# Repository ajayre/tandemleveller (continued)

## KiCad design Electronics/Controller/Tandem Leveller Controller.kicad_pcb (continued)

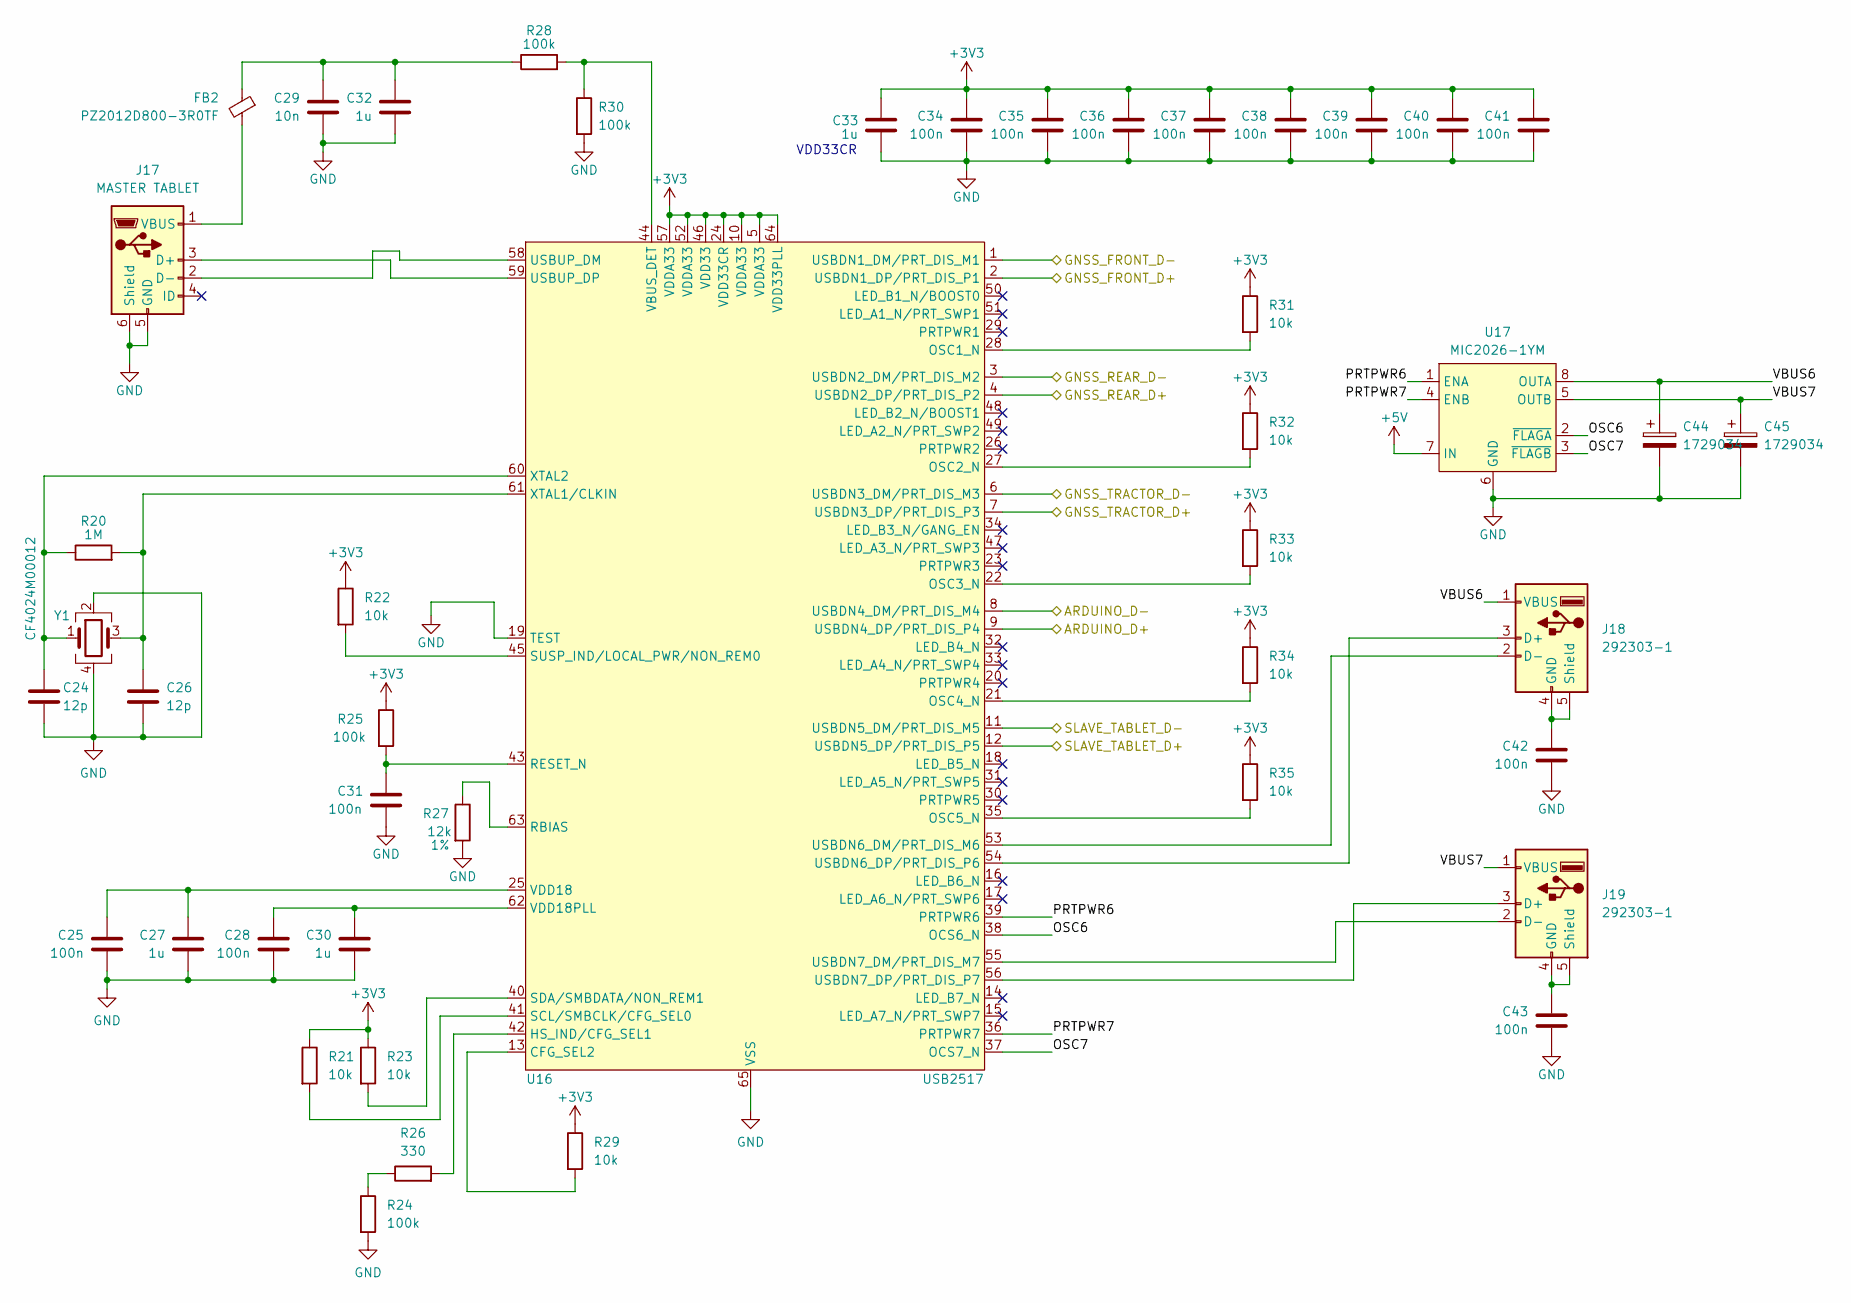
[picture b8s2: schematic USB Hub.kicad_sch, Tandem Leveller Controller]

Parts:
C24, C26: 12p; C_0805_2012Metric; LCSC C1792
C25, C28, C31, C34, C35, C36, C37, C38, C39, C40, C41, C42, C43: 100n; C_0805_2012Metric; LCSC C1711
C27, C30, C32, C33: 1u; C_0805_2012Metric; LCSC C24123
C29: 10n; C_0805_2012Metric; LCSC C1710
C44, C45: 1729034; CP_Elec_6.3x5.9; LCSC C340733
FB2: PZ2012D800-3R0TF; R_0805_2012Metric; LCSC C12389
J17: MASTER TABLET; USB_Micro-B_Amphenol_10103594-0001LF_Horizontal; LCSC C428495
J18, J19: 292303-1; LCSC C86461
R20: 1M; R_0805_2012Metric; LCSC C17514
R21, R22, R23, R29, R31, R32, R33, R34, R35: 10k; R_0805_2012Metric; LCSC C17414
R24, R25, R28, R30: 100k; R_0805_2012Metric; LCSC C17407
R26: 330; R_0805_2012Metric; LCSC C17630
R27: 12k; R_0805_2012Metric; Tolerance 1%; LCSC C17444
U16: USB2517; QFN-64-1EP_9x9mm_P0.5mm_EP4.7x4.7mm_ThermalVias; LCSC C1521556
U17: MIC2026-1YM; SOIC-8_3.9x4.9mm_P1.27mm; LCSC C144190
Y1: CF4024M00012; FA-238; LCSC C5765976

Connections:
+3V3: C33.1, C34.1, C35.1, C36.1, C37.1, C38.1, C39.1, C40.1, C41.1, R21.1, R22.1, R23.1, R25.1, R29.1, R31.1, R32.1, R33.1, R34.1, R35.1, U16.5 (VDDA33), U16.10 (VDDA33), U16.24 (VDD33CR), U16.46 (VDD33), U16.52 (VDDA33), U16.57 (VDDA33), U16.64 (VDD33PLL); also elsewhere on the board
+5V: U17.7 (IN); also elsewhere on the board
/Slave Tablet/SLAVE_TABLET_D+: U16.12 (USBDN5_DP/PRT_DIS_P5); also elsewhere on the board
/Slave Tablet/SLAVE_TABLET_D-: U16.11 (USBDN5_DM/PRT_DIS_M5); also elsewhere on the board
/USB Devices/ARDUINO_D+: U16.9 (USBDN4_DP/PRT_DIS_P4); also elsewhere on the board
/USB Devices/ARDUINO_D-: U16.8 (USBDN4_DM/PRT_DIS_M4); also elsewhere on the board
/USB Devices/GNSS_FRONT_D+: U16.2 (USBDN1_DP/PRT_DIS_P1); also elsewhere on the board
/USB Devices/GNSS_FRONT_D-: U16.1 (USBDN1_DM/PRT_DIS_M1); also elsewhere on the board
/USB Devices/GNSS_REAR_D+: U16.4 (USBDN2_DP/PRT_DIS_P2); also elsewhere on the board
/USB Devices/GNSS_REAR_D-: U16.3 (USBDN2_DM/PRT_DIS_M2); also elsewhere on the board
/USB Devices/GNSS_TRACTOR_D+: U16.7 (USBDN3_DP/PRT_DIS_P3); also elsewhere on the board
/USB Devices/GNSS_TRACTOR_D-: U16.6 (USBDN3_DM/PRT_DIS_M3); also elsewhere on the board
/USB Hub/OSC6: U16.38 (OCS6_N), U17.2 (~FLAGA)
/USB Hub/OSC7: U16.37 (OCS7_N), U17.3 (~FLAGB)
/USB Hub/PRTPWR6: U16.39 (PRTPWR6), U17.1 (ENA)
/USB Hub/PRTPWR7: U16.36 (PRTPWR7), U17.4 (ENB)
/USB Hub/VBUS6: C44.1, J18.1 (VBUS), U17.8 (OUTA)
/USB Hub/VBUS7: C45.1, J19.1 (VBUS), U17.5 (OUTB)
GND: C24.2, C25.2, C26.2, C27.2, C28.2, C29.2, C30.2, C31.2, C32.2, C33.2, C34.2, C35.2, C36.2, C37.2, C38.2, C39.2, C40.2, C41.2, C42.2, C43.2, C44.2, C45.2, J17.5 (GND), J17.6 (Shield), R24.2, R27.2, R30.2, U16.19 (TEST), U16.65 (VSS), U17.6 (GND), Y1.2, Y1.4; also elsewhere on the board
unnamed: C29.1, C32.1, FB2.1, R28.1
unnamed: J17.3 (D+), U16.59 (USBUP_DP)
unnamed: J17.2 (D-), U16.58 (USBUP_DM)
unnamed: FB2.2, J17.1 (VBUS)
unnamed: J18.3 (D+), U16.54 (USBDN6_DP/PRT_DIS_P6)
unnamed: J18.2 (D-), U16.53 (USBDN6_DM/PRT_DIS_M6)
unnamed: C42.1, J18.4 (GND), J18.5 (Shield)
unnamed: J19.3 (D+), U16.56 (USBDN7_DP/PRT_DIS_P7)
unnamed: J19.2 (D-), U16.55 (USBDN7_DM/PRT_DIS_M7)
unnamed: C43.1, J19.4 (GND), J19.5 (Shield)
unnamed: R24.1, R26.1
unnamed: R29.2, U16.13 (CFG_SEL2)
unnamed: R26.2, U16.42 (HS_IND/CFG_SEL1)
unnamed: R31.2, U16.28 (OSC1_N)
unnamed: R32.2, U16.27 (OSC2_N)
unnamed: R33.2, U16.22 (OSC3_N)
unnamed: R34.2, U16.21 (OSC4_N)
unnamed: R35.2, U16.35 (OSC5_N)
unnamed: R27.1, U16.63 (RBIAS)
unnamed: C31.1, R25.2, U16.43 (RESET_N)
unnamed: R21.2, U16.41 (SCL/SMBCLK/CFG_SEL0)
unnamed: R23.2, U16.40 (SDA/SMBDATA/NON_REM1)
unnamed: R22.2, U16.45 (SUSP_IND/LOCAL_PWR/NON_REM0)
unnamed: R28.2, R30.1, U16.44 (VBUS_DET)
unnamed: C25.1, C27.1, U16.25 (VDD18)
unnamed: C28.1, C30.1, U16.62 (VDD18PLL)
unnamed: C26.1, R20.2, U16.61 (XTAL1/CLKIN), Y1.3
unnamed: C24.1, R20.1, U16.60 (XTAL2), Y1.1

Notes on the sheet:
VDD33CR

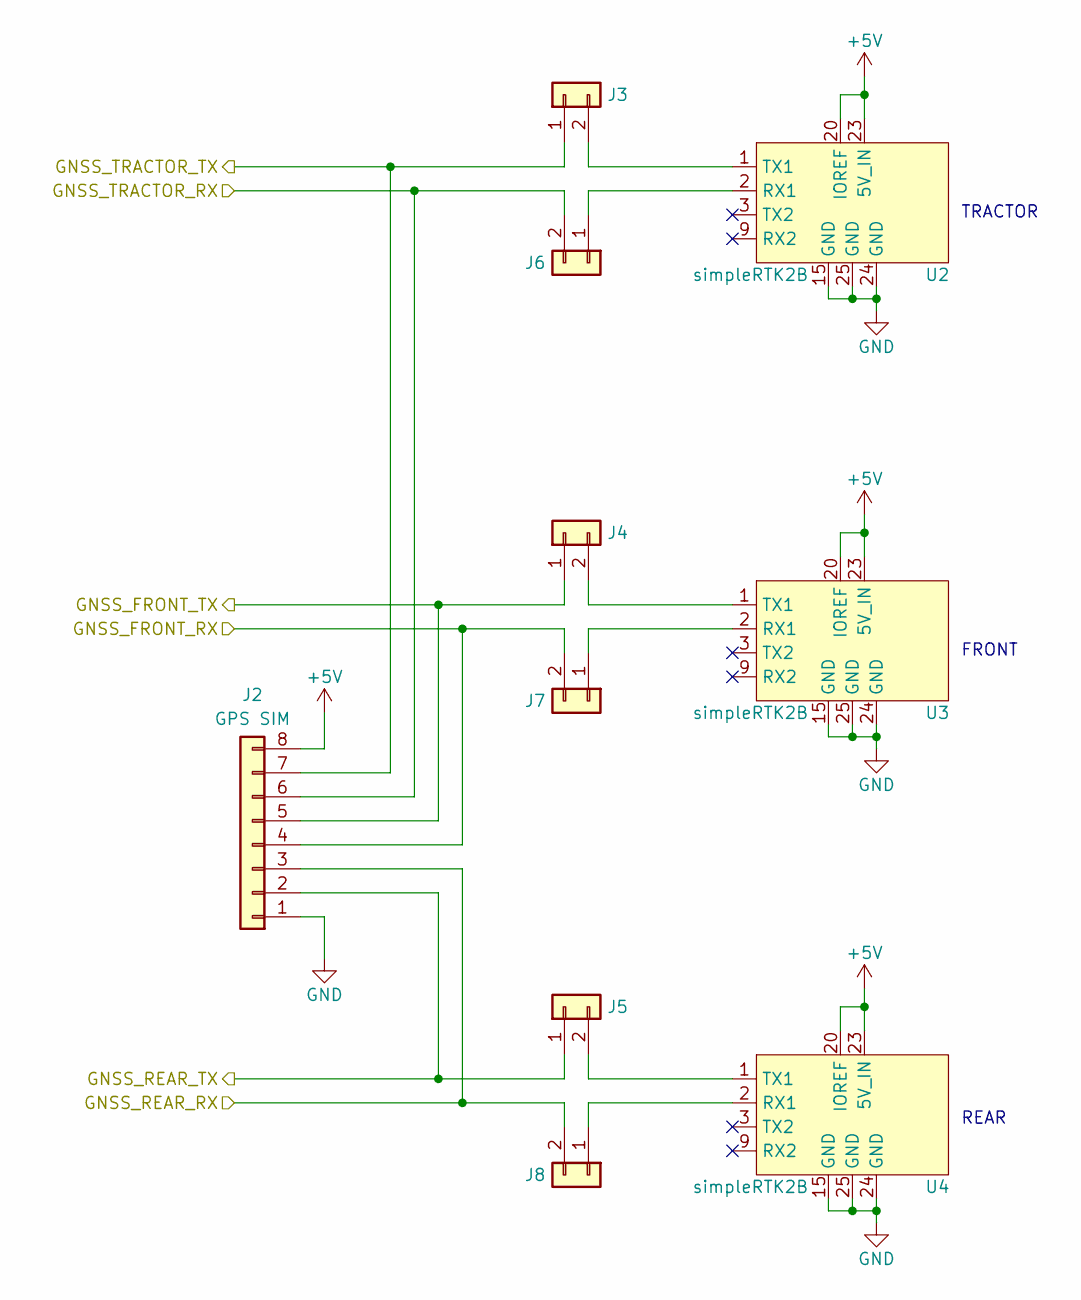
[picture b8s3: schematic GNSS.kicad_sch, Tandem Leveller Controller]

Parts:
J2: GPS SIM; JST_PH_B8B-PH-K_1x08_P2.00mm_Vertical; LCSC C157974
J3, J4, J5, J6, J7, J8: Conn_01x02; PinHeader_1x02_P2.54mm_Vertical; LCSC C7494857
U2, U3, U4: simpleRTK2B

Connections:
+5V: J2.8, U2.20 (IOREF), U2.23 (5V_IN), U3.20 (IOREF), U3.23 (5V_IN), U4.20 (IOREF), U4.23 (5V_IN); also elsewhere on the board
/GNSS/GNSS_FRONT_RX: J2.4, J7.2; also elsewhere on the board
/GNSS/GNSS_FRONT_TX: J2.5, J4.1; also elsewhere on the board
/GNSS/GNSS_REAR_RX: J2.3, J8.2; also elsewhere on the board
/GNSS/GNSS_REAR_TX: J2.2, J5.1; also elsewhere on the board
/GNSS/GNSS_TRACTOR_RX: J2.6, J6.2; also elsewhere on the board
/GNSS/GNSS_TRACTOR_TX: J2.7, J3.1; also elsewhere on the board
GND: J2.1, U2.15 (GND), U2.24 (GND), U2.25 (GND), U3.15 (GND), U3.24 (GND), U3.25 (GND), U4.15 (GND), U4.24 (GND), U4.25 (GND); also elsewhere on the board
unnamed: J3.2, U2.1 (TX1)
unnamed: J4.2, U3.1 (TX1)
unnamed: J5.2, U4.1 (TX1)
unnamed: J6.1, U2.2 (RX1)
unnamed: J7.1, U3.2 (RX1)
unnamed: J8.1, U4.2 (RX1)

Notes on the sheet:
FRONT
REAR
TRACTOR

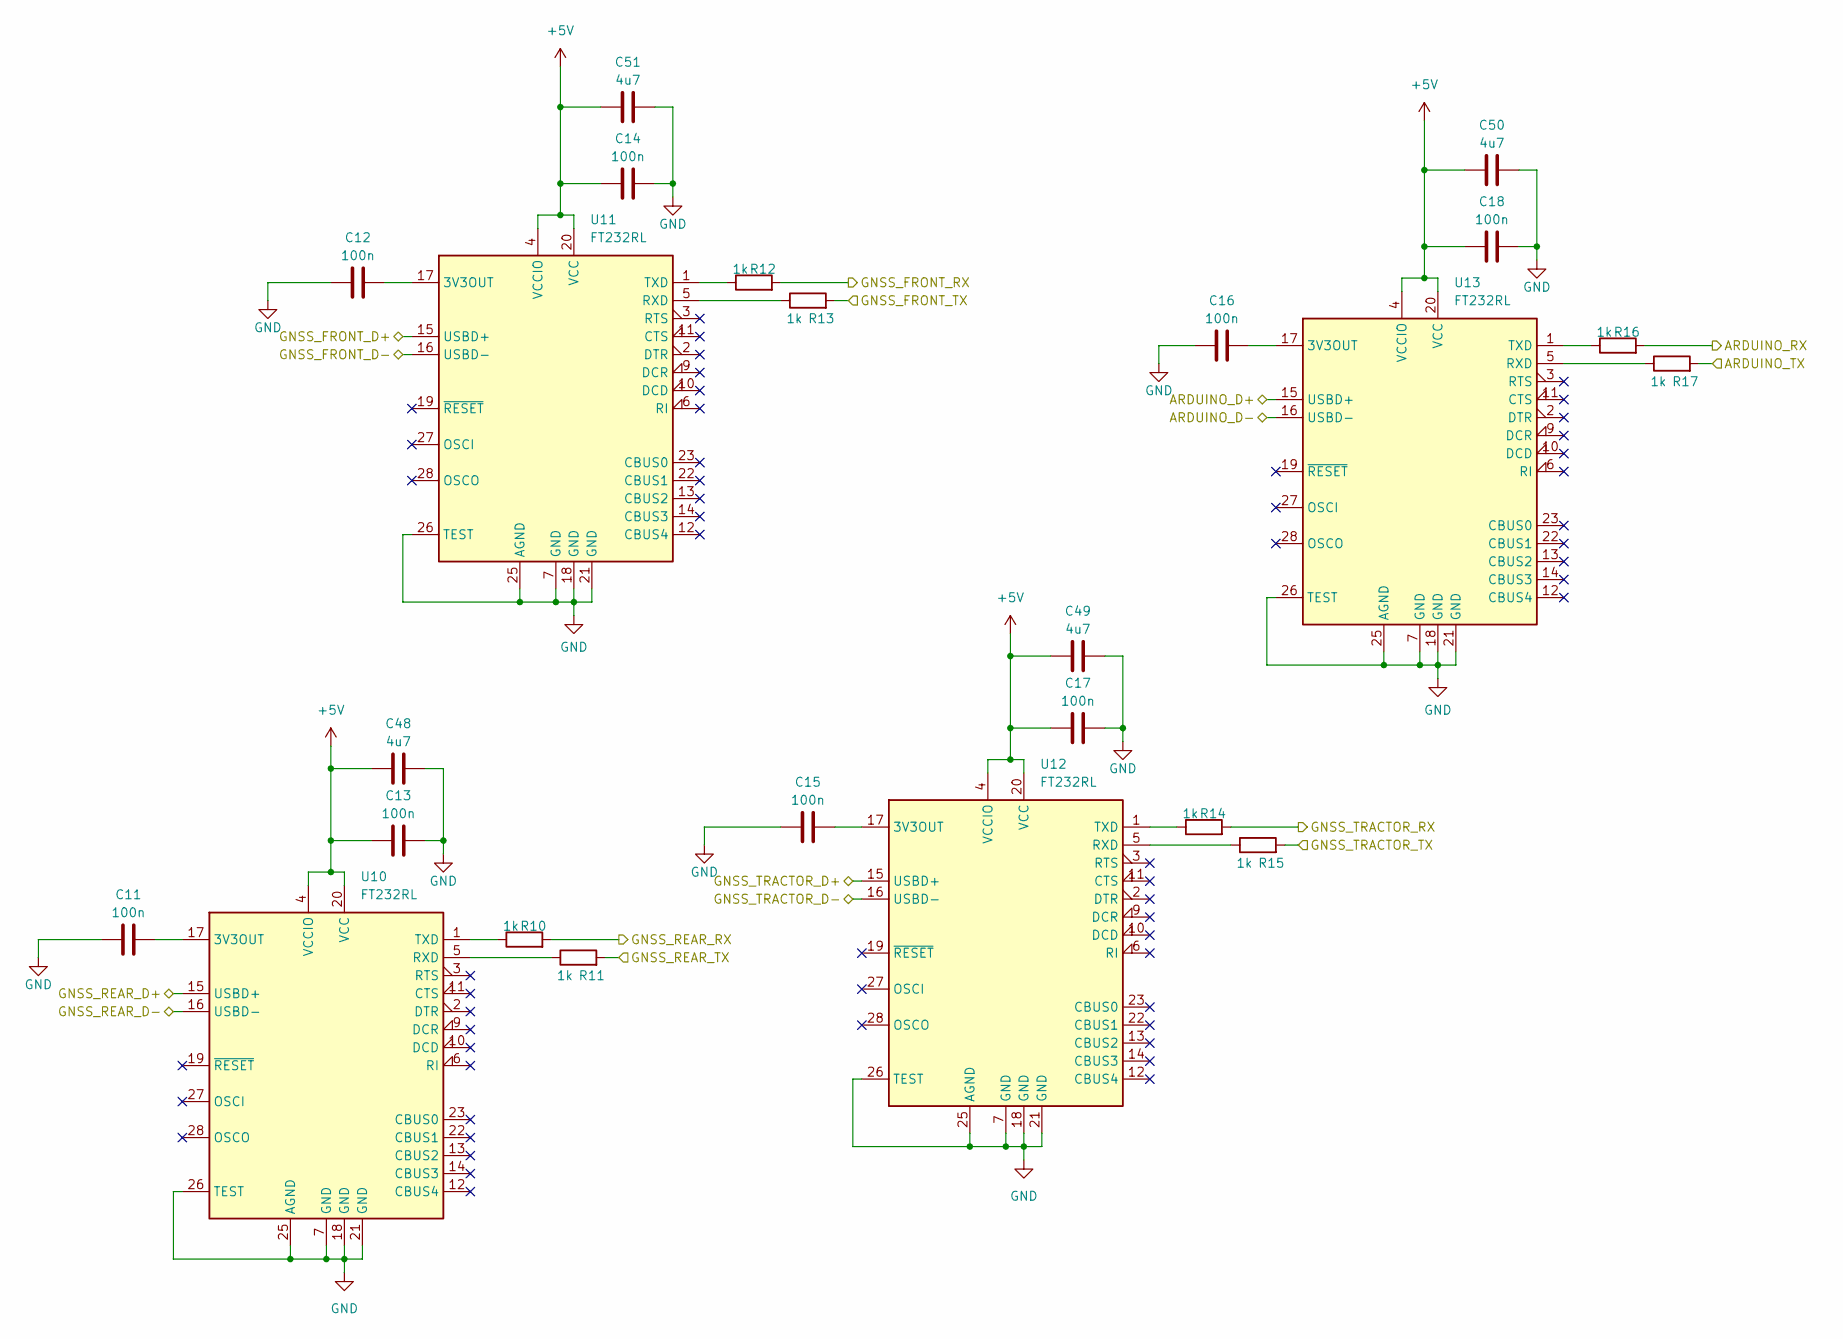
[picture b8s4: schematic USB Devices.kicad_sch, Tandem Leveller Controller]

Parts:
C11, C12, C13, C14, C15, C16, C17, C18: 100n; C_0805_2012Metric; LCSC C1711
C48, C49, C50, C51: 4u7; C_0805_2012Metric; LCSC C1779
R10, R11, R12, R13, R14, R15, R16, R17: 1k; R_0805_2012Metric; LCSC C17513
U10, U11, U12, U13: FT232RL; SSOP-28_5.3x10.2mm_P0.65mm; LCSC C8690

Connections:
+5V: C13.1, C14.1, C17.1, C18.1, C48.1, C49.1, C50.1, C51.1, U10.4 (VCCIO), U10.20 (VCC), U11.4 (VCCIO), U11.20 (VCC), U12.4 (VCCIO), U12.20 (VCC), U13.4 (VCCIO), U13.20 (VCC); also elsewhere on the board
/GNSS/GNSS_FRONT_RX: R12.2; also elsewhere on the board
/GNSS/GNSS_FRONT_TX: R13.2; also elsewhere on the board
/GNSS/GNSS_REAR_RX: R10.2; also elsewhere on the board
/GNSS/GNSS_REAR_TX: R11.2; also elsewhere on the board
/GNSS/GNSS_TRACTOR_RX: R14.2; also elsewhere on the board
/GNSS/GNSS_TRACTOR_TX: R15.2; also elsewhere on the board
/USB Devices/ARDUINO_D+: U13.15 (USBD+); also elsewhere on the board
/USB Devices/ARDUINO_D-: U13.16 (USBD-); also elsewhere on the board
/USB Devices/ARDUINO_RX: R16.2; also elsewhere on the board
/USB Devices/ARDUINO_TX: R17.2; also elsewhere on the board
/USB Devices/GNSS_FRONT_D+: U11.15 (USBD+); also elsewhere on the board
/USB Devices/GNSS_FRONT_D-: U11.16 (USBD-); also elsewhere on the board
/USB Devices/GNSS_REAR_D+: U10.15 (USBD+); also elsewhere on the board
/USB Devices/GNSS_REAR_D-: U10.16 (USBD-); also elsewhere on the board
/USB Devices/GNSS_TRACTOR_D+: U12.15 (USBD+); also elsewhere on the board
/USB Devices/GNSS_TRACTOR_D-: U12.16 (USBD-); also elsewhere on the board
GND: C11.1, C12.1, C13.2, C14.2, C15.1, C16.1, C17.2, C18.2, C48.2, C49.2, C50.2, C51.2, U10.7 (GND), U10.18 (GND), U10.21 (GND), U10.25 (AGND), U10.26 (TEST), U11.7 (GND), U11.18 (GND), U11.21 (GND), U11.25 (AGND), U11.26 (TEST), U12.7 (GND), U12.18 (GND), U12.21 (GND), U12.25 (AGND), U12.26 (TEST), U13.7 (GND), U13.18 (GND), U13.21 (GND), U13.25 (AGND), U13.26 (TEST); also elsewhere on the board
unnamed: C11.2, U10.17 (3V3OUT)
unnamed: R11.1, U10.5 (RXD)
unnamed: R10.1, U10.1 (TXD)
unnamed: C12.2, U11.17 (3V3OUT)
unnamed: R13.1, U11.5 (RXD)
unnamed: R12.1, U11.1 (TXD)
unnamed: C15.2, U12.17 (3V3OUT)
unnamed: R15.1, U12.5 (RXD)
unnamed: R14.1, U12.1 (TXD)
unnamed: C16.2, U13.17 (3V3OUT)
unnamed: R17.1, U13.5 (RXD)
unnamed: R16.1, U13.1 (TXD)

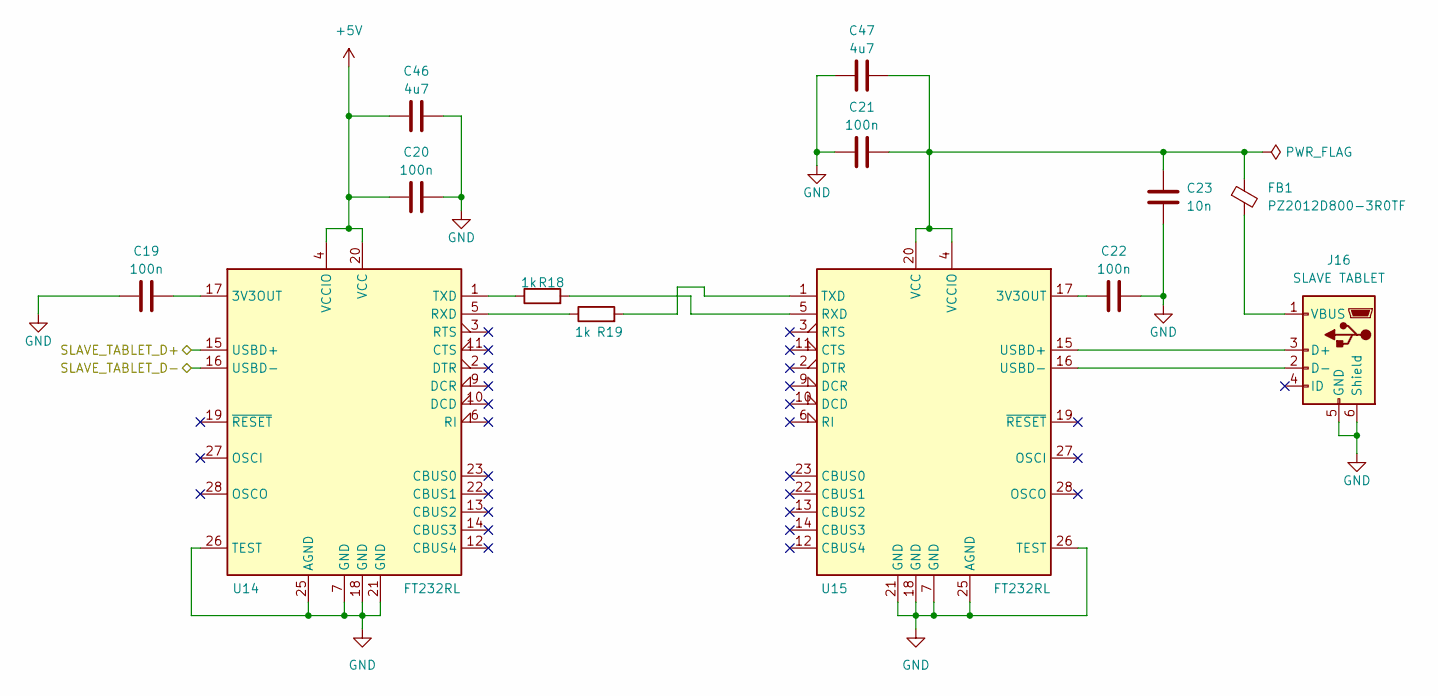
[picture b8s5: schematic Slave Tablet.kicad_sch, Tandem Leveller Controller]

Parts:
C19, C20, C21, C22: 100n; C_0805_2012Metric; LCSC C1711
C23: 10n; C_0805_2012Metric; LCSC C1710
C46, C47: 4u7; C_0805_2012Metric; LCSC C1779
FB1: PZ2012D800-3R0TF; R_0805_2012Metric; LCSC C12389
J16: SLAVE TABLET; USB_Micro-B_Amphenol_10103594-0001LF_Horizontal; LCSC C428495
R18, R19: 1k; R_0805_2012Metric; LCSC C17513
U14, U15: FT232RL; SSOP-28_5.3x10.2mm_P0.65mm; LCSC C8690

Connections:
+5V: C20.1, C46.1, U14.4 (VCCIO), U14.20 (VCC); also elsewhere on the board
/Slave Tablet/SLAVE_TABLET_D+: U14.15 (USBD+); also elsewhere on the board
/Slave Tablet/SLAVE_TABLET_D-: U14.16 (USBD-); also elsewhere on the board
GND: C19.1, C20.2, C21.2, C22.1, C23.2, C46.2, C47.1, J16.5 (GND), J16.6 (Shield), U14.7 (GND), U14.18 (GND), U14.21 (GND), U14.25 (AGND), U14.26 (TEST), U15.7 (GND), U15.18 (GND), U15.21 (GND), U15.25 (AGND), U15.26 (TEST); also elsewhere on the board
unnamed: J16.3 (D+), U15.15 (USBD+)
unnamed: J16.2 (D-), U15.16 (USBD-)
unnamed: FB1.2, J16.1 (VBUS)
unnamed: C19.2, U14.17 (3V3OUT)
unnamed: R19.1, U14.5 (RXD)
unnamed: R18.1, U14.1 (TXD)
unnamed: C22.2, U15.17 (3V3OUT)
unnamed: R18.2, U15.5 (RXD)
unnamed: R19.2, U15.1 (TXD)
unnamed: C21.1, C23.1, C47.2, FB1.1, U15.4 (VCCIO), U15.20 (VCC)

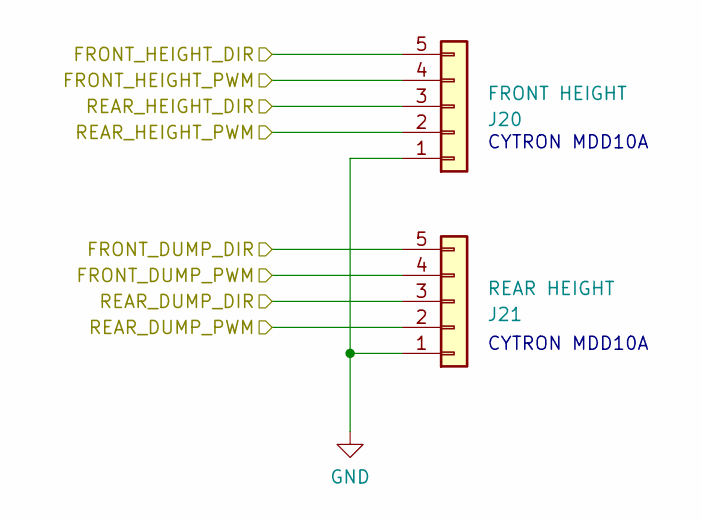
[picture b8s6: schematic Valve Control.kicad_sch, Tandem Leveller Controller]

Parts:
J20: FRONT HEIGHT; JST_PH_B5B-PH-K_1x05_P2.00mm_Vertical; LCSC C157993
J21: REAR HEIGHT; JST_PH_B5B-PH-K_1x05_P2.00mm_Vertical; LCSC C157993

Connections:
/Valve Control/FRONT_DUMP_DIR: J21.5; also elsewhere on the board
/Valve Control/FRONT_DUMP_PWM: J21.4; also elsewhere on the board
/Valve Control/FRONT_HEIGHT_DIR: J20.5; also elsewhere on the board
/Valve Control/FRONT_HEIGHT_PWM: J20.4; also elsewhere on the board
/Valve Control/REAR_DUMP_DIR: J21.3; also elsewhere on the board
/Valve Control/REAR_DUMP_PWM: J21.2; also elsewhere on the board
/Valve Control/REAR_HEIGHT_DIR: J20.3; also elsewhere on the board
/Valve Control/REAR_HEIGHT_PWM: J20.2; also elsewhere on the board
GND: J20.1, J21.1; also elsewhere on the board

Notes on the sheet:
CYTRON MDD10A

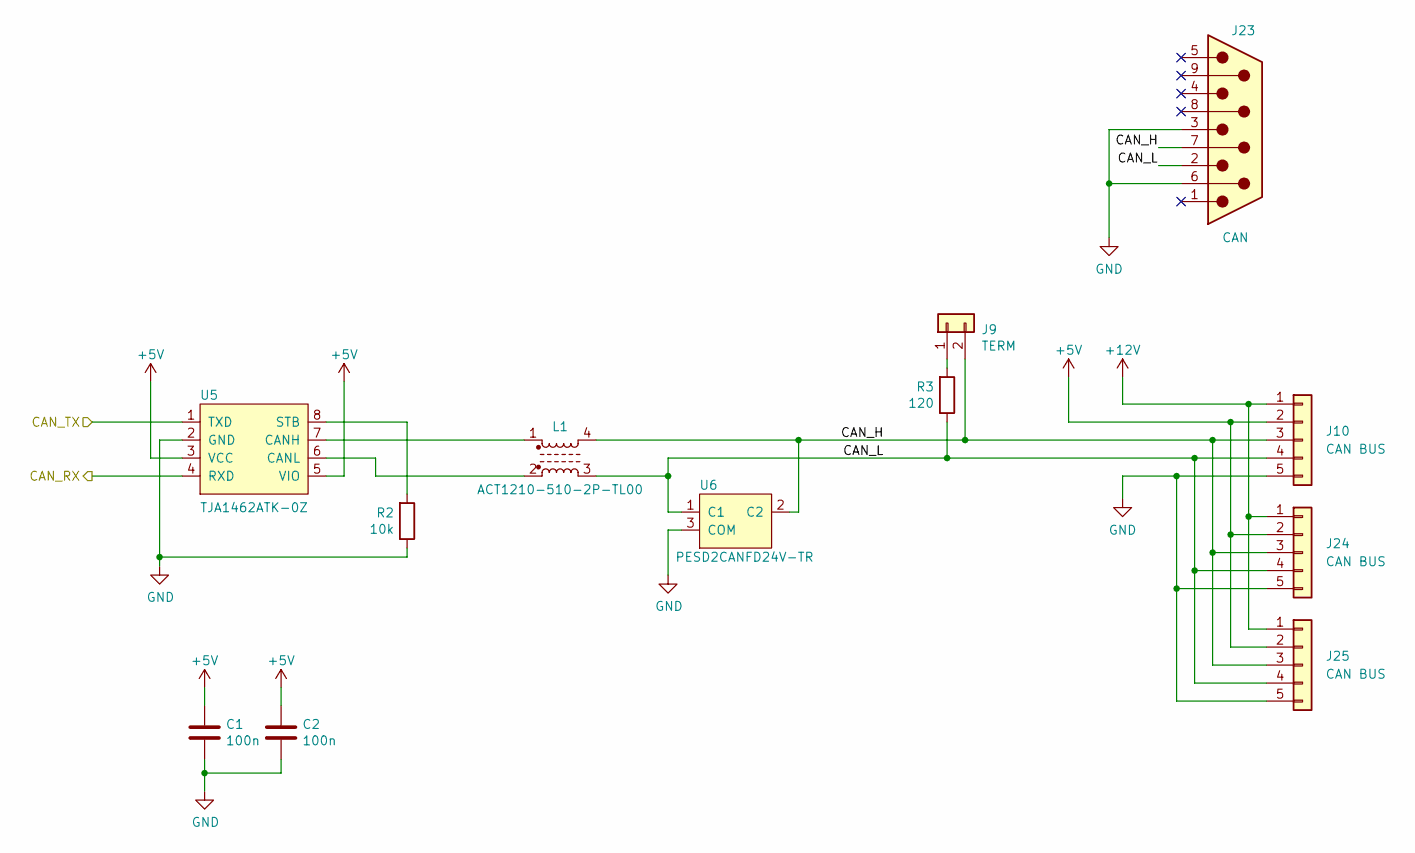
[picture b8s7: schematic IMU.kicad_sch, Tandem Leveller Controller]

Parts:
C1, C2: 100n; C_0805_2012Metric; LCSC C1711
J9: TERM; PinHeader_1x02_P2.54mm_Vertical; LCSC C7494857
J10, J24, J25: CAN BUS; JST_PH_B5B-PH-K_1x05_P2.00mm_Vertical; LCSC C157993
J23: CAN; DB9_RA_MALE_LD09P13A4; LCSC C3103673
L1: ACT1210-510-2P-TL00; LCSC C95572
R2: 10k; R_0805_2012Metric; LCSC C17414
R3: 120; R_0805_2012Metric; LCSC C17437
U5: TJA1462ATK-0Z; HVSON8_0_65mm; LCSC C3229259
U6: PESD2CANFD24V-TR; SOT-23; LCSC C552486

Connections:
+5V: C1.1, C2.1, J10.2, J24.2, J25.2, U5.3 (VCC), U5.5 (VIO); also elsewhere on the board
+12V: J10.1, J24.1, J25.1; also elsewhere on the board
/CAN/CAN_H: J9.2, J10.3, J23.7, J24.3, J25.3, L1.4, U6.2 (C2)
/CAN/CAN_L: J10.4, J23.2, J24.4, J25.4, L1.3, R3.1, U6.1 (C1)
/CAN/CAN_RX: U5.4 (RXD); also elsewhere on the board
/CAN/CAN_TX: U5.1 (TXD); also elsewhere on the board
GND: C1.2, C2.2, J10.5, J23.3, J23.6, J24.5, J25.5, R2.1, U5.2 (GND), U6.3 (COM); also elsewhere on the board
unnamed: J9.1, R3.2
unnamed: L1.1, U5.7 (CANH)
unnamed: L1.2, U5.6 (CANL)
unnamed: R2.2, U5.8 (STB)

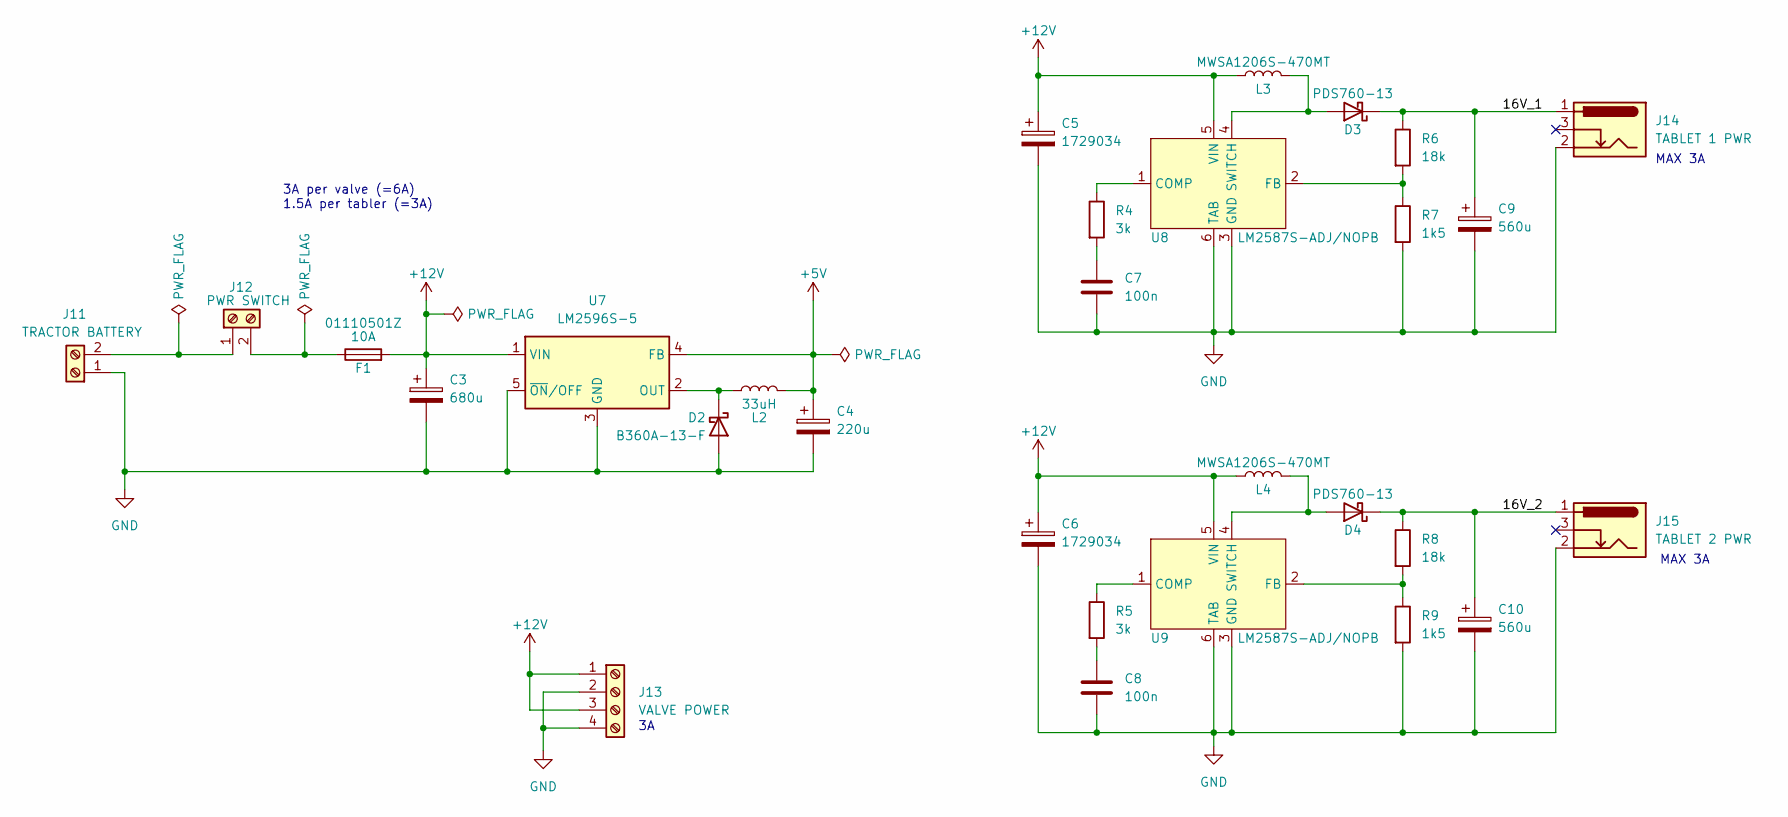
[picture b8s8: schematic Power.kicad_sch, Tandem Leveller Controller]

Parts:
C3: 680u; CP_Elec_10x10.5; LCSC C50456
C4: 220u; CP_Elec_8x6.5; LCSC C3340
C5, C6: 1729034; CP_Elec_6.3x5.9; LCSC C340733
C7, C8: 100n; C_0805_2012Metric; LCSC C1711
C9, C10: 560u; CP_Elec_10x10.5; LCSC C1984785
D2: B360A-13-F; D_SMA; LCSC C6807778
D3, D4: PDS760-13; D_PowerDI-5; LCSC C3018534
F1: 10A; 5x20 Fuse Holder; LCSC C151075
J11: TRACTOR BATTERY; PhoenixContact_COMBICON_MKDSN_2; LCSC C3820334
J12: PWR SWITCH; PhoenixContact_COMBICON_MKDSN_2; LCSC C3820334
J13: VALVE POWER; PhoenixContact_COMBICON_PT_4; LCSC C7032066
J14: TABLET 1 PWR; BarrelJack_Wuerth_6941xx301002; LCSC C5441017
J15: TABLET 2 PWR; BarrelJack_Wuerth_6941xx301002; LCSC C5441017
L2: 33uH; MWSA0603S-330MT; LCSC C408454
L3, L4: MWSA1206S-470MT; LCSC C408531
R4, R5: 3k; R_0805_2012Metric; LCSC C17661
R6, R8: 18k; R_0805_2012Metric; LCSC C17506
R7, R9: 1k5; R_0805_2012Metric; LCSC C4310
U7: LM2596S-5; TO-263-5_TabPin3; LCSC C5276750
U8, U9: LM2587S-ADJ/NOPB; TO-263-5_TabPin6; LCSC C1355343

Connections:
+5V: C4.1, L2.2, U7.4 (FB); also elsewhere on the board
+12V: C3.1, C5.1, C6.1, F1.2, J13.1, J13.3, L3.1, L4.1, U7.1 (VIN), U8.5 (VIN), U9.5 (VIN); also elsewhere on the board
/Power/16V_1: C9.1, D3.1 (K), J14.1, R6.1
/Power/16V_2: C10.1, D4.1 (K), J15.1, R8.1
GND: C3.2, C4.2, C5.2, C6.2, C7.2, C8.2, C9.2, C10.2, D2.2 (A), J11.1, J13.2, J13.4, J14.2, J15.2, R7.2, R9.2, U7.3 (GND), U7.5 (~ON/OFF), U8.3 (GND), U8.6 (TAB), U9.3 (GND), U9.6 (TAB); also elsewhere on the board
unnamed: C7.1, R4.2
unnamed: C8.1, R5.2
unnamed: D2.1 (K), L2.1, U7.2 (OUT)
unnamed: D3.2 (A), L3.2, U8.4 (SWITCH)
unnamed: D4.2 (A), L4.2, U9.4 (SWITCH)
unnamed: J11.2, J12.1
unnamed: F1.1, J12.2
unnamed: R4.1, U8.1 (COMP)
unnamed: R6.2, R7.1, U8.2 (FB)
unnamed: R5.1, U9.1 (COMP)
unnamed: R8.2, R9.1, U9.2 (FB)

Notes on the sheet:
MAX 3A
3A per valve (=6A) 1.5A per tabler (=3A)

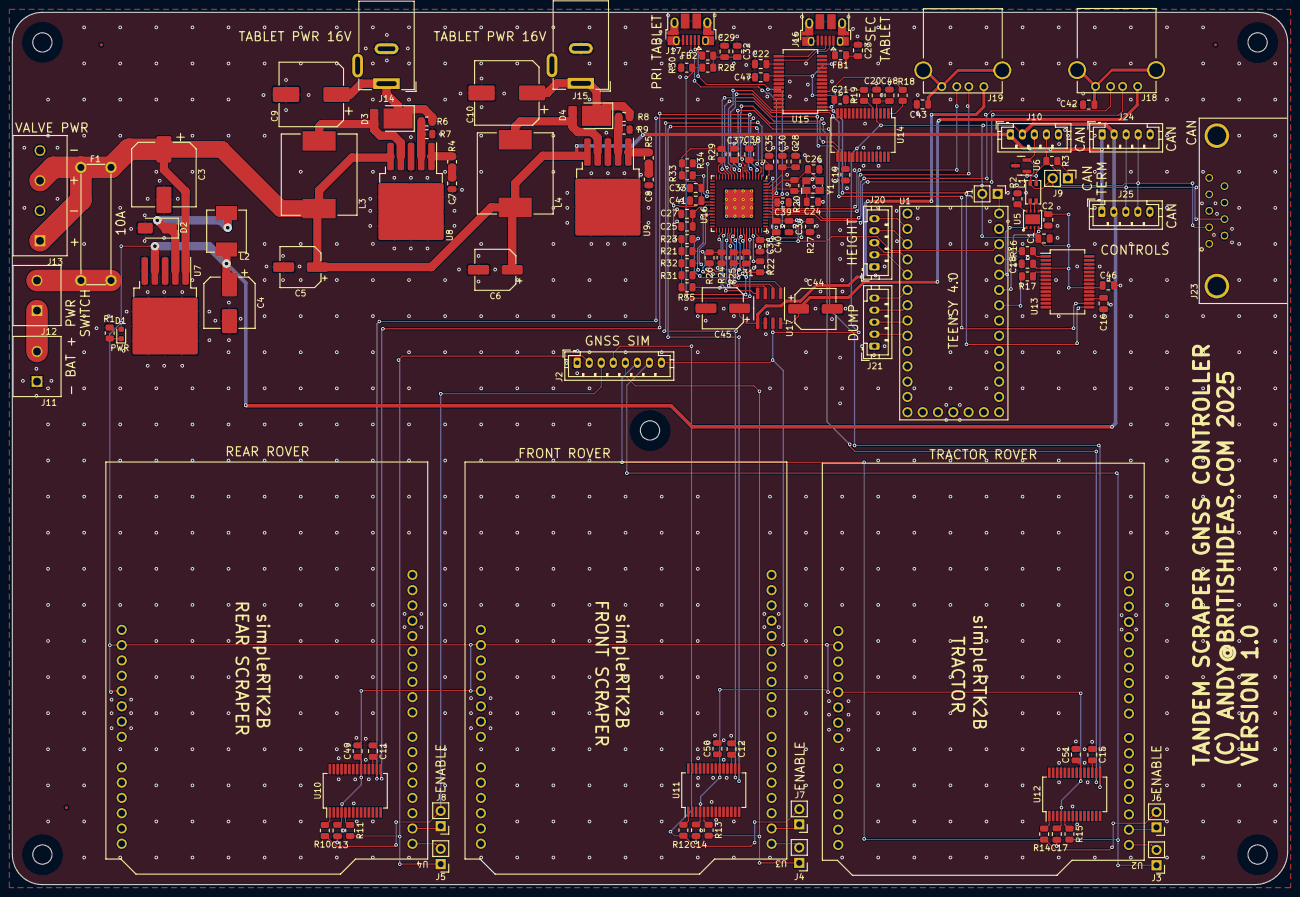
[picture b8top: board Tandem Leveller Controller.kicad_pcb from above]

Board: 2 copper layers, 212.0 x 145.0 mm, 142 parts (0 on the bottom side), 115 nets.

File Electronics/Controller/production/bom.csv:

Designator,Footprint,Quantity,Value,LCSC Part #
"C1, C11, C12, C13, C14, C15, C16, C17, C18, C19, C2, C20, C21, C22, C25, C28, C31, C34, C35, C36, C37, C38, C39, C40, C41, C42, C43, C7, C8",0805,29,100n,C1711
"C10, C9",CP_Elec_10x10.5,2,560u,C1984785
"C23, C29",0805,2,10n,C1710
"C24, C26",0805,2,12p,C1792
"C27, C30, C32, C33",0805,4,1u,C24123
C3,CP_Elec_10x10.5,1,680u,C50456
C4,CP_Elec_8x6.5,1,220u,C3340
"C44, C45, C5, C6",CP_Elec_6.3x5.9,4,1729034,C340733
"C46, C47, C48, C49, C50, C51",0805,6,4u7,C1779
D1,0603,1,APTD1608SECK,C5879220
D2,D_SMA,1,B360A-13-F,C6807778
"D3, D4",D_PowerDI-5,2,PDS760-13,C3018534
F1,5x20 Fuse Holder,1,10A,C151075
"FB1, FB2",0805,2,PZ2012D800-3R0TF,C12389
"FID1, FID2, FID3",Fiducial_0.5mm_Mask1mm,3,Fiducial,
"J1, J3, J4, J5, J6, J7, J8",PinHeader_1x02_P2.54mm_Vertical,7,Conn_01x02,C7494857
"J10, J24, J25",JST_PH_B5B-PH-K_1x05_P2.00mm_Vertical,3,CAN BUS,C157993
J11,PhoenixContact_COMBICON_MKDSN_2,1,TRACTOR BATTERY,C3820334
J12,PhoenixContact_COMBICON_MKDSN_2,1,PWR SWITCH,C3820334
J13,PhoenixContact_COMBICON_PT_4,1,VALVE POWER,C7032066
J14,BarrelJack_Wuerth_6941xx301002,1,TABLET 1 PWR,C5441017
J15,BarrelJack_Wuerth_6941xx301002,1,TABLET 2 PWR,C5441017
J16,USB_Micro-B_Amphenol_10103594-0001LF_Horizontal,1,SLAVE TABLET,C428495
J17,USB_Micro-B_Amphenol_10103594-0001LF_Horizontal,1,MASTER TABLET,C428495
"J18, J19",292303-1,2,292303-1,C86461
J2,JST_PH_B8B-PH-K_1x08_P2.00mm_Vertical,1,GPS SIM,C157974
J20,JST_PH_B5B-PH-K_1x05_P2.00mm_Vertical,1,FRONT HEIGHT,C157993
J21,JST_PH_B5B-PH-K_1x05_P2.00mm_Vertical,1,REAR HEIGHT,C157993
J23,DB9_RA_MALE_LD09P13A4,1,CAN,C3103673
J9,PinHeader_1x02_P2.54mm_Vertical,1,TERM,C7494857
L1,ACT1210-510-2P-TL00,1,ACT1210-510-2P-TL00,C95572
L2,MWSA0603S-330MT,1,33uH,C408454
"L3, L4",MWSA1206S-470MT,2,MWSA1206S-470MT,C408531
"R1, R26",0805,2,330,C17630
"R10, R11, R12, R13, R14, R15, R16, R17, R18, R19",0805,10,1k,C17513
"R2, R21, R22, R23, R29, R31, R32, R33, R34, R35",0805,10,10k,C17414
R20,0805,1,1M,C17514
"R24, R25, R28, R30",0805,4,100k,C17407
R27,0805,1,12k,C17444
R3,0805,1,120,C17437
"R4, R5",0805,2,3k,C17661
"R6, R8",0805,2,18k,C17506
"R7, R9",0805,2,1k5,C4310
U1,Teensy_4.0,1,TEENSY 4.0,
"U10, U11, U12, U13, U14, U15",SSOP-28_5.3x10.2mm_P0.65mm,6,FT232RL,C8690
U16,QFN-64-1EP_9x9mm_P0.5mm_EP4.7x4.7mm_ThermalVias,1,USB2517,C1521556
U17,SOIC-8_3.9x4.9mm_P1.27mm,1,MIC2026-1YM,C144190
"U2, U3, U4",simpleRTK2B,3,simpleRTK2B,
U5,HVSON8_0_65mm,1,TJA1462ATK-0Z,C3229259
U6,SOT-23,1,PESD2CANFD24V-TR,C552486
U7,TO-263-5_TabPin3,1,LM2596S-5,C5276750
"U8, U9",TO-263-5_TabPin6,2,LM2587S-ADJ/NOPB,C1355343
Y1,FA-238,1,CF4024M00012,C5765976

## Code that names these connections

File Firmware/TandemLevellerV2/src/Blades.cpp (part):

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#include "Blades.h"

// GPIO pins
#define FRONT_HEIGHT_DIR 0
#define FRONT_HEIGHT_PWM 1
#define REAR_HEIGHT_DIR  2
#define REAR_HEIGHT_PWM  3
#define FRONT_DUMP_DIR   4
#define FRONT_DUMP_PWM   5
#define REAR_DUMP_DIR    6
#define REAR_DUMP_PWM    7

// from EHPR98-G35 specs
#define PWM_FREQUENCY_HZ 120
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  analogWriteResolution(8); // 0 - 255

  // set up direction control signals
  pinMode(FRONT_HEIGHT_DIR, OUTPUT);
  pinMode(REAR_HEIGHT_DIR,  OUTPUT);
  pinMode(FRONT_DUMP_DIR,   OUTPUT);
  pinMode(REAR_DUMP_DIR,    OUTPUT);

  // initalize direction
  digitalWrite(FRONT_HEIGHT_DIR, LOW);
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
